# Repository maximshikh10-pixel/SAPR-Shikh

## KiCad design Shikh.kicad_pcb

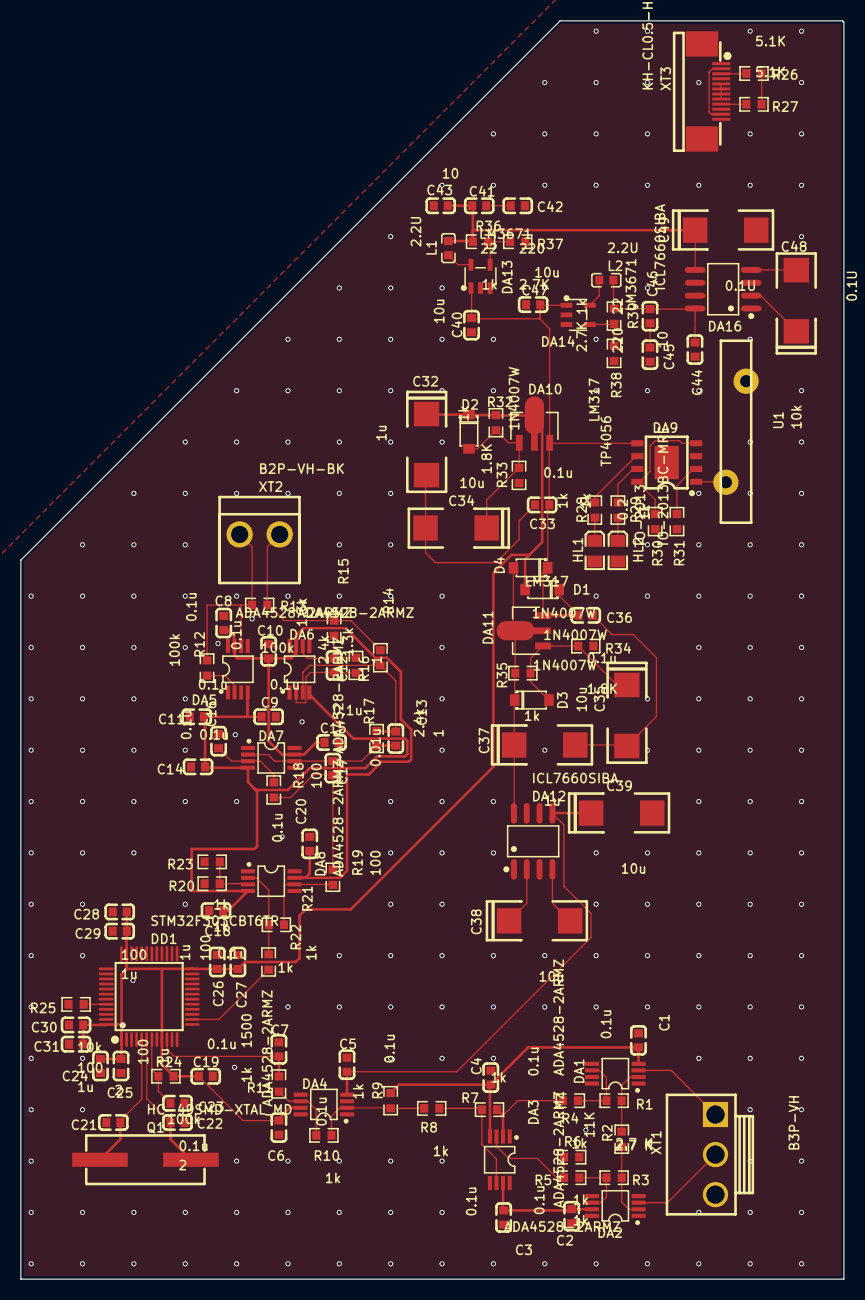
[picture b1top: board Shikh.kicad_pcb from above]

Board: 2 copper layers, 81.4 x 124.5 mm, 117 parts (0 on the bottom side), 66 nets.

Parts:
C1, C2, C3, C4, C5, C6, C8, C9, C10, C11, C14, C15, C16, C18, C19, C20, C23, C33, C36: 0.1u; C0603
C7: 1500; C0603
C12, C13: 1; C0603
C17: 0.01u; C0603
C21, C22: 2; C0603
C24, C27, C28, C30: 100; C0603
C25, C26, C29, C31: 1u; C0603
C32, C37: 1u; CASE-C_6032
C34, C35, C38, C39: 10u; CASE-C_6032
C40, C47: 10u; C0603
C41, C46: 22; C0603
C42, C45: 220; C0603
C43, C44: 10; C0603
C48, C49: 0.1U; CASE-C_6032
D1, D2, D3, D4: 1N4007W; SOD-123_L2.8-W1.8-LS3.7-RD
DA1, DA2, DA3, DA4, DA5, DA6, DA7, DA8: ADA4528-2ARMZ; MSOP-8_L3.0-W3.0-P0.65-LS4.9-BL
DA9: TP4056; ESOP-8_L4.9-W3.9-P1.27-LS6.0-BL-EP
DA10, DA11: LM317; SOT-89-3_L4.5-W2.4-P1.50-LS4.0-BR
DA12, DA16: ICL7660SIBA; SOIC-8_L4.9-W3.9-P1.27-LS6.0-BL
DA13, DA14: LM3671; SOT-23-5_L3.0-W1.7-P0.95-LS2.8-BL
DD1: STM32F303CBT6TR; LQFP-48_L7.0-W7.0-P0.50-LS9.0-BL
HL1: TO-2013; 0805-DIODE
HL2: TO-2013BC-MRE; 0805-DIODE
L1, L2: 2.2U; L0603
Q1: HC-49SMD-XTAL_MD; CRYSTAL-SMD_L11.4-W4.8-LS12.7
R1, R3: 2.7 K; R0603
R2: 11K; R0603
R4, R5, R6, R7, R8, R9, R10, R11, R20, R21, R22, R23, R28, R29, R31, R32, R35, R36, R39: 1k; R0603
R12, R13, R24: 100k; R0603
R14, R15: 1.3k; R0603
R16, R17: 2.4k; R0603
R18, R19: 100; R0603
R25: 10k; R0603
R26, R27: 5.1K; R0603
R30: 0.2; R0603
R33, R34: 1.8K; R0603
R37, R38: 2.7K; R0603
U1: 10k; ВАРИСТОР B72220-S 271-K101 (S20K275), 275 В, 151 ДЖ
XT1: B3P-VH; CONN-TH_B3P-VH-LF-SN
XT2: B2P-VH-BK; CONN-TH_B2P-VH-BK
XT3: KH-CL0.5-H2.0-12PIN; FPC-SMD_KH-CL0.5-H2.0-12PIN

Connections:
+1,8V: C2.2, C3.2, DA2.7, DA3.7
+3,6V: C6.1, C19.1, C24.1, C25.1, C26.1, C27.1, C28.1, C29.1, C30.1, C31.1, C32.1, D1.2, D2.1, DA4.7, DA10.2, DD1.1, DD1.9, DD1.24, DD1.35, DD1.48, R24.1, R32.2
+3.6V: C8.1, C10.1, C15.1, C20.1, DA5.7, DA6.7, DA7.7, DA8.7
+5V: XT3.2, XT3.11
-1,8V: C1.1, C4.2, DA1.4, DA3.4, R9.2
-1.8V: C41.2, C43.2, C49.1, DA16.5, L1.2, R36.2
-3,6V: C5.2, C39.1, DA4.4, DA12.5
-3.6V: C9.1, C11.2, C14.2, C18.1, DA5.4, DA6.4, DA7.4, DA8.4
ADC1_IN2: C7.1, DD1.10, R11.2
ADC1_OUT1: DD1.14, R22.2
C32_2: C32.2, C33.1, C34.2
C35_2: C35.2, C36.1, C37.2
C37_1: C37.1, D3.1, D4.2, DA11.2, DA12.8, R35.2
C41_1: C41.1, C42.2
C44_2: C44.2, C46.2, DA16.8, L2.2, R39.2
C45_2: C45.2, C46.1
DA1_2: DA1.2, R1.1, R2.2
DA1_6: DA1.6, R1.2, R4.1
DA2_2: DA2.2, R2.1, R3.2
DA2_6: DA2.6, R3.1, R5.1
DA4_2: DA4.2, R8.2, R9.1, R10.1
DA4_6: DA4.6, R10.2, R11.1
DA5_2: DA5.2, R12.1
DA6_2: C12.2, DA6.2, R16.1
DA6_3: C13.1, DA6.3, R14.1, R17.1
DA6_6: C12.1, DA6.6, R15.1, R16.2
DA7_3: C16.1, DA7.3, R18.1
DA8_2: DA8.2, R21.2, R22.1
DA8_3: DA8.3, R20.1, R23.1
DA9_1: DA9.1, U1.2
DA9_2: DA9.2, R31.2
DA9_5: C33.2, C36.2, C40.2, C47.2, D1.1, D4.1, DA9.5, DA10.3, DA11.3, DA13.1, DA14.1
DA10_1: C34.1, D2.2, DA10.1, R32.1, R33.2
DA12_2: C38.1, DA12.2
DA12_4: C38.2, DA12.4
DA16_2: C48.1, DA16.2
DA16_4: C48.2, DA16.4
DD1_5: C21.2, DD1.5, Q1.1
DD1_6: C22.2, DD1.6, Q1.2
DD1_7: C23.2, DD1.7, R24.2
DD1_44: DD1.44, R25.1
GND: C1.2, C2.1, C3.1, C4.1, C5.1, C6.2, C7.2, C8.2, C9.2, C10.2, C11.1, C14.1, C15.2, C16.2, C18.2, C19.2, C20.2, C21.1, C22.1, C23.1, C24.2, C25.2, C26.2, C27.2, C28.2, C29.2, C30.2, C31.2, C39.2, C40.1, C42.1, C43.1, C44.1, C45.1, C47.1, C49.2, DA4.3, DA9.3, DA12.3, DA12.6, DA13.3, DA14.3, DA16.3, DA16.6, DD1.8, DD1.23, DD1.36, DD1.47, HL1.1, HL2.1, R6.1, R20.2, R25.2, R30.1, R31.1, R33.1, R34.1, R37.1, R38.1, U1.1, XT1.3, XT3.1, XT3.12
HL1_2: HL1.2, R28.1
HL2_2: HL2.2, R29.1
L1_1: DA13.5, L1.1
L2_1: DA14.5, L2.1
R4_2: DA3.2, R4.2, R7.2
R5_2: DA3.3, R5.2, R6.2
R7_1: DA3.6, R7.1, R8.1
R17_2: C13.2, C17.1, DA7.2, DA7.6, R17.2
R18_2: C17.2, R18.2, R19.1
R19_2: DA8.6, R19.2, R21.1
R26_2: R26.2, R27.2
R28_2: DA9.6, R28.2
R29_2: DA9.7, R29.2
R30_2: DA9.4, DA9.8, R30.2
R34_2: C35.1, D3.2, DA11.1, R34.2, R35.1
R36_1: DA13.4, R36.1, R37.2
R38_2: DA14.4, R38.2, R39.1
XT1_1: DA1.3, XT1.1
XT1_2: DA2.3, XT1.2
XT2_1: DA5.6, R12.2, R13.2, XT2.1
XT2_2: R13.1, R14.2, R15.2, XT2.2
XT3_3: R26.1, XT3.3
XT3_5: XT3.5, XT3.6, XT3.7, XT3.8
XT3_9: R27.1, XT3.9
